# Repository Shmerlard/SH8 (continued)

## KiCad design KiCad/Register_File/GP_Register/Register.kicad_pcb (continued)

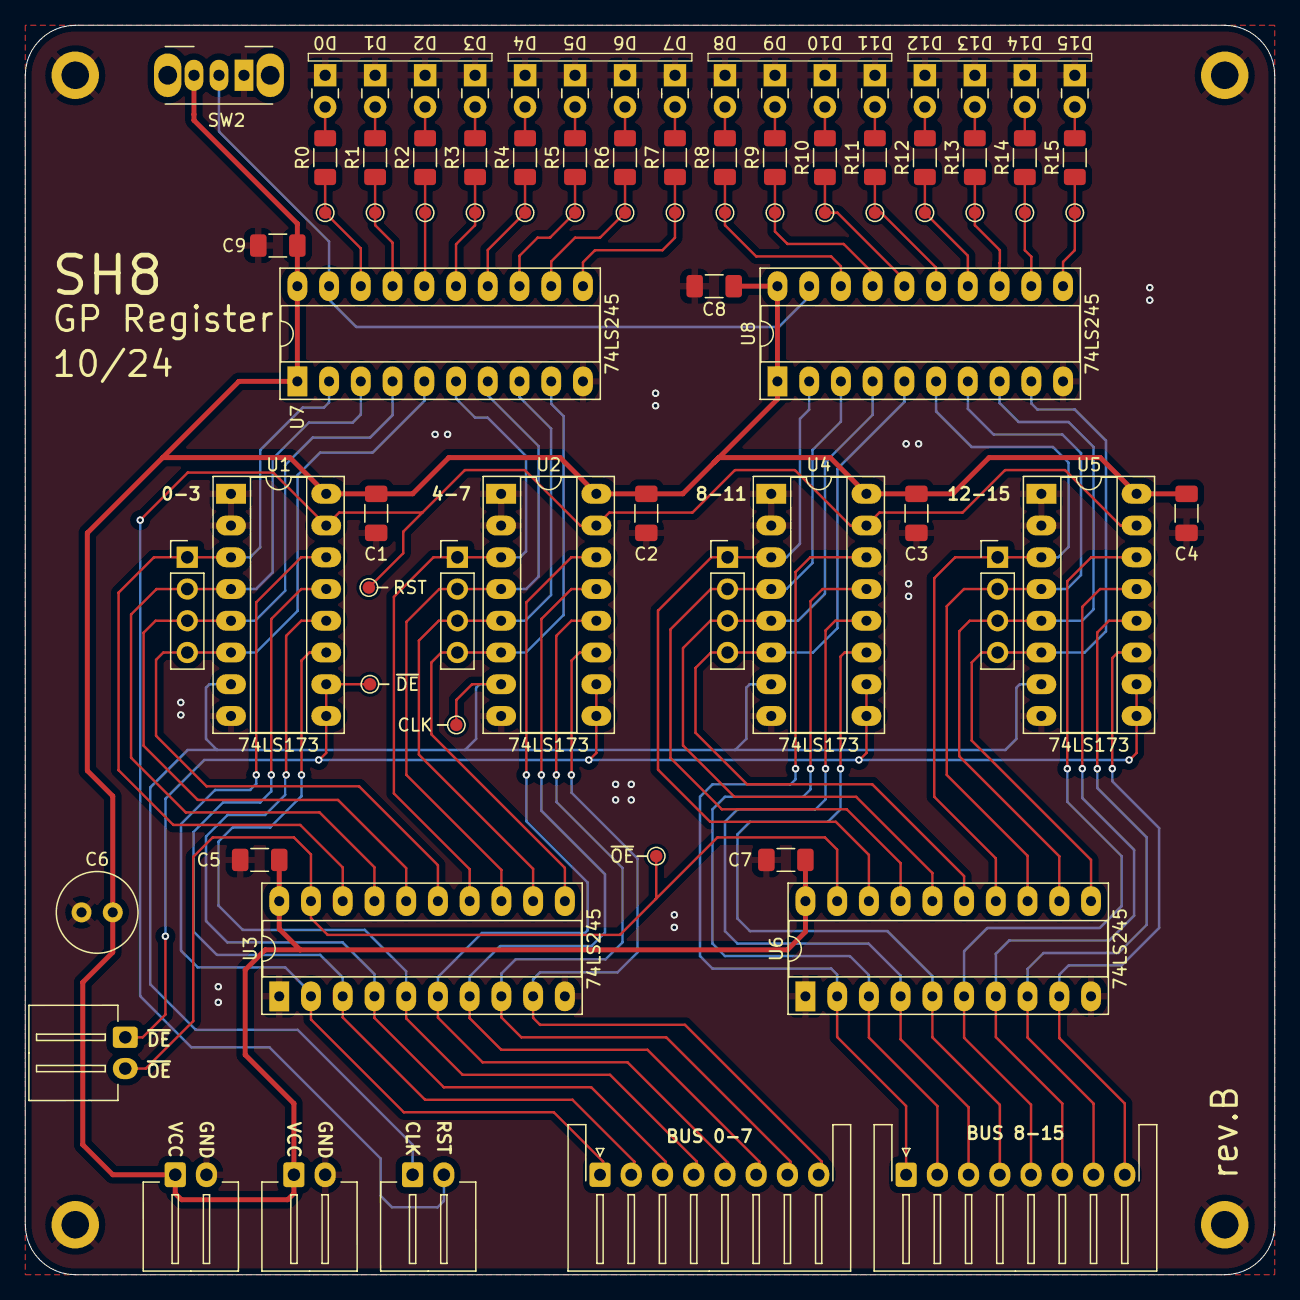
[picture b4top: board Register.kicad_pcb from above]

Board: 2 copper layers, 100.0 x 100.0 mm, 84 parts (0 on the bottom side), 71 nets.

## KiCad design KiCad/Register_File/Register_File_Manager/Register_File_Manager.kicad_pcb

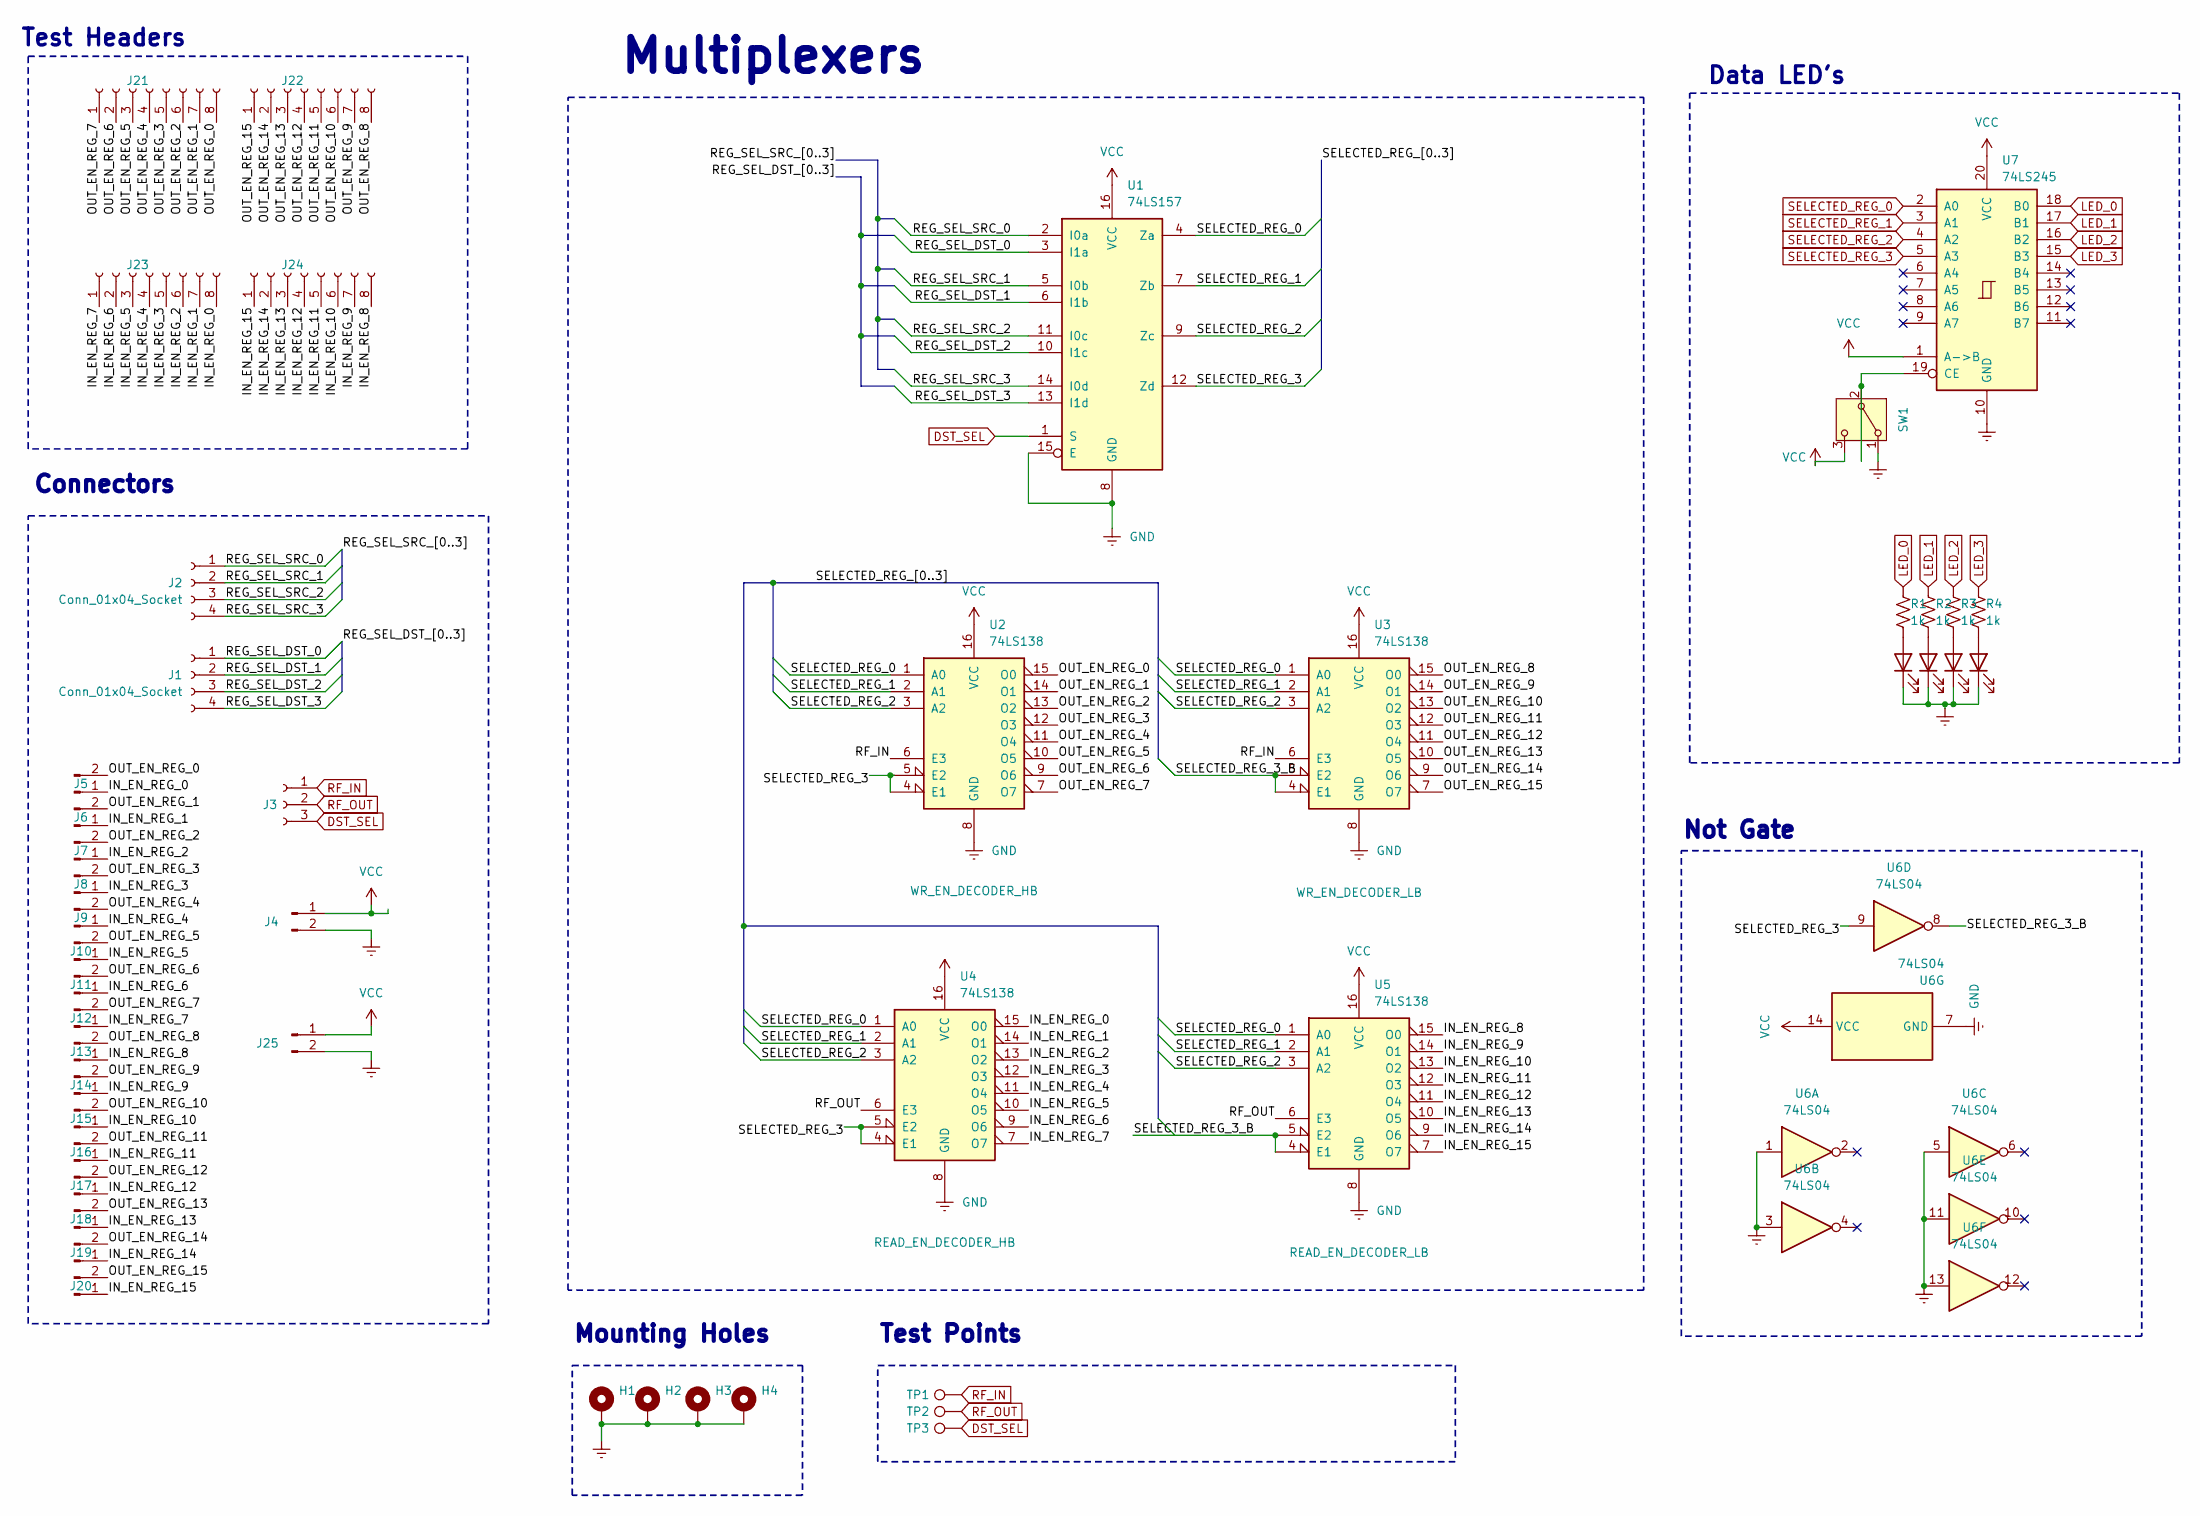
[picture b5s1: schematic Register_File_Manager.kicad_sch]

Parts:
D1, D2, D3, D4: LED; LED_Rectangular_W3.0mm_H2.0mm
H1, H2, H3, H4: MountingHole_Pad; MountingHole_2.2mm_M2_DIN965_Pad
J1, J2: Conn_01x04_Socket; JST_XH_S4B-XH-A-1_1x04_P2.50mm_Horizontal
J3: Conn_01x03_Socket; JST_XH_S3B-XH-A-1_1x03_P2.50mm_Horizontal
J4, J5, J6, J7, J8, J9, J10, J11, J12, J13, J14, J15, J16, J17, J18, J19, J20, J25: Conn_01x02_Socket; JST_XH_S2B-XH-A-1_1x02_P2.50mm_Horizontal
J21, J22, J23, J24: Conn_01x08_Socket; PinHeader_1x08_P2.54mm_Vertical
R1, R2, R3, R4: 1k; R_1206_3216Metric_Pad1.30x1.75mm_HandSolder
SW1: SW_SPDT; SW_Slide_SPDT_Angled_CK_OS102011MA1Q
TP1, TP2, TP3: TestPoint; TestPoint_Pad_D1.0mm
U1: 74LS157; DIP-16_W7.62mm_Socket_LongPads
U2, U3, U4, U5: 74LS138; DIP-16_W7.62mm_Socket_LongPads
U6: 74LS04
U7: 74LS245; DIP-20_W7.62mm_Socket_LongPads

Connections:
/IN_EN_REG_0: J5.1, J23.8, U4.15 (O0)
/IN_EN_REG_1: J6.1, J23.7, U4.14 (O1)
/IN_EN_REG_2: J7.1, J23.6, U4.13 (O2)
/IN_EN_REG_3: J8.1, J23.5, U4.12 (O3)
/IN_EN_REG_4: J9.1, J23.4, U4.11 (O4)
/IN_EN_REG_5: J10.1, J23.3, U4.10 (O5)
/IN_EN_REG_6: J11.1, J23.2, U4.9 (O6)
/IN_EN_REG_7: J12.1, J23.1, U4.7 (O7)
/IN_EN_REG_8: J13.1, J24.8, U5.15 (O0)
/IN_EN_REG_9: J14.1, J24.7, U5.14 (O1)
/IN_EN_REG_10: J15.1, J24.6, U5.13 (O2)
/IN_EN_REG_11: J16.1, J24.5, U5.12 (O3)
/IN_EN_REG_12: J17.1, J24.4, U5.11 (O4)
/IN_EN_REG_13: J18.1, J24.3, U5.10 (O5)
/IN_EN_REG_14: J19.1, J24.2, U5.9 (O6)
/IN_EN_REG_15: J20.1, J24.1, U5.7 (O7)
/OUT_EN_REG_0: J5.2, J21.8, U2.15 (O0)
/OUT_EN_REG_1: J6.2, J21.7, U2.14 (O1)
/OUT_EN_REG_2: J7.2, J21.6, U2.13 (O2)
/OUT_EN_REG_3: J8.2, J21.5, U2.12 (O3)
/OUT_EN_REG_4: J9.2, J21.4, U2.11 (O4)
/OUT_EN_REG_5: J10.2, J21.3, U2.10 (O5)
/OUT_EN_REG_6: J11.2, J21.2, U2.9 (O6)
/OUT_EN_REG_7: J12.2, J21.1, U2.7 (O7)
/OUT_EN_REG_8: J13.2, J22.8, U3.15 (O0)
/OUT_EN_REG_9: J14.2, J22.7, U3.14 (O1)
/OUT_EN_REG_10: J15.2, J22.6, U3.13 (O2)
/OUT_EN_REG_11: J16.2, J22.5, U3.12 (O3)
/OUT_EN_REG_12: J17.2, J22.4, U3.11 (O4)
/OUT_EN_REG_13: J18.2, J22.3, U3.10 (O5)
/OUT_EN_REG_14: J19.2, J22.2, U3.9 (O6)
/OUT_EN_REG_15: J20.2, J22.1, U3.7 (O7)
/REG_SEL_DST_0: J1.1, U1.3 (I1a)
/REG_SEL_DST_1: J1.2, U1.6 (I1b)
/REG_SEL_DST_2: J1.3, U1.10 (I1c)
/REG_SEL_DST_3: J1.4, U1.13 (I1d)
/REG_SEL_SRC_0: J2.1, U1.2 (I0a)
/REG_SEL_SRC_1: J2.2, U1.5 (I0b)
/REG_SEL_SRC_2: J2.3, U1.11 (I0c)
/REG_SEL_SRC_3: J2.4, U1.14 (I0d)
/SELECTED_REG_3_B: U3.4 (E1), U3.5 (E2), U5.4 (E1), U5.5 (E2), U6.8
DST_SEL: J3.3, TP3.1, U1.1 (S)
GND: D1.1 (K), D2.1 (K), D3.1 (K), D4.1 (K), H1.1, H2.1, H3.1, H4.1, J4.2, J25.2, SW1.1 (A), U1.8 (GND), U1.15 (E), U2.8 (GND), U3.8 (GND), U4.8 (GND), U5.8 (GND), U6.1, U6.3, U6.5, U6.7 (GND), U6.11, U6.13, U7.10 (GND)
LED_0: R1.1, U7.18 (B0)
LED_1: R2.1, U7.17 (B1)
LED_2: R3.1, U7.16 (B2)
LED_3: R4.1, U7.15 (B3)
unnamed: D1.2 (A), R1.2
unnamed: D2.2 (A), R2.2
unnamed: D3.2 (A), R3.2
unnamed: D4.2 (A), R4.2
unnamed: SW1.2 (B), U7.19 (CE)
RF_IN: J3.1, TP1.1, U2.6 (E3), U3.6 (E3)
RF_OUT: J3.2, TP2.1, U4.6 (E3), U5.6 (E3)
SELECTED_REG_0: U1.4 (Za), U2.1 (A0), U3.1 (A0), U4.1 (A0), U5.1 (A0), U7.2 (A0)
SELECTED_REG_1: U1.7 (Zb), U2.2 (A1), U3.2 (A1), U4.2 (A1), U5.2 (A1), U7.3 (A1)
SELECTED_REG_2: U1.9 (Zc), U2.3 (A2), U3.3 (A2), U4.3 (A2), U5.3 (A2), U7.4 (A2)
SELECTED_REG_3: U1.12 (Zd), U2.4 (E1), U2.5 (E2), U4.4 (E1), U4.5 (E2), U6.9, U7.5 (A3)
VCC: J4.1, J25.1, SW1.3 (C), U1.16 (VCC), U2.16 (VCC), U3.16 (VCC), U4.16 (VCC), U5.16 (VCC), U6.14 (VCC), U7.1 (A->B), U7.20 (VCC)

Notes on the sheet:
Connectors
Test Points
Mounting Holes
Test Headers
Multiplexers
Data LED's
Not Gate

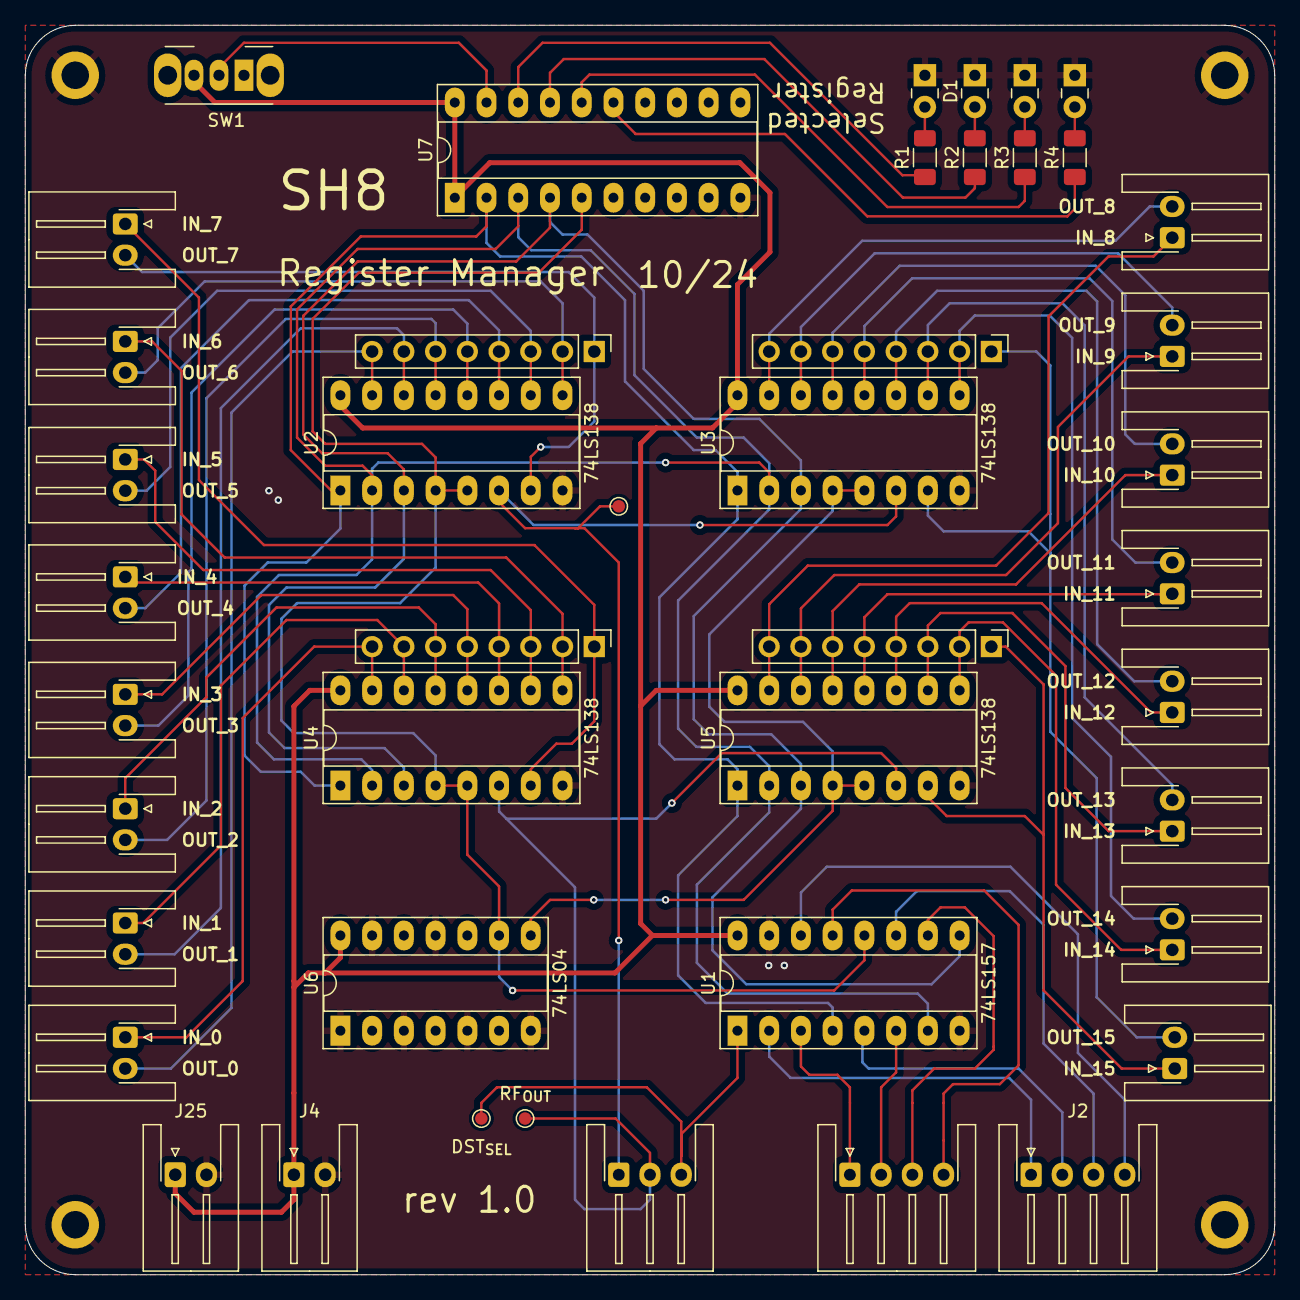
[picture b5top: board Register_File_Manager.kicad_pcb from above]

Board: 2 copper layers, 100.0 x 100.0 mm, 48 parts (0 on the bottom side), 59 nets.

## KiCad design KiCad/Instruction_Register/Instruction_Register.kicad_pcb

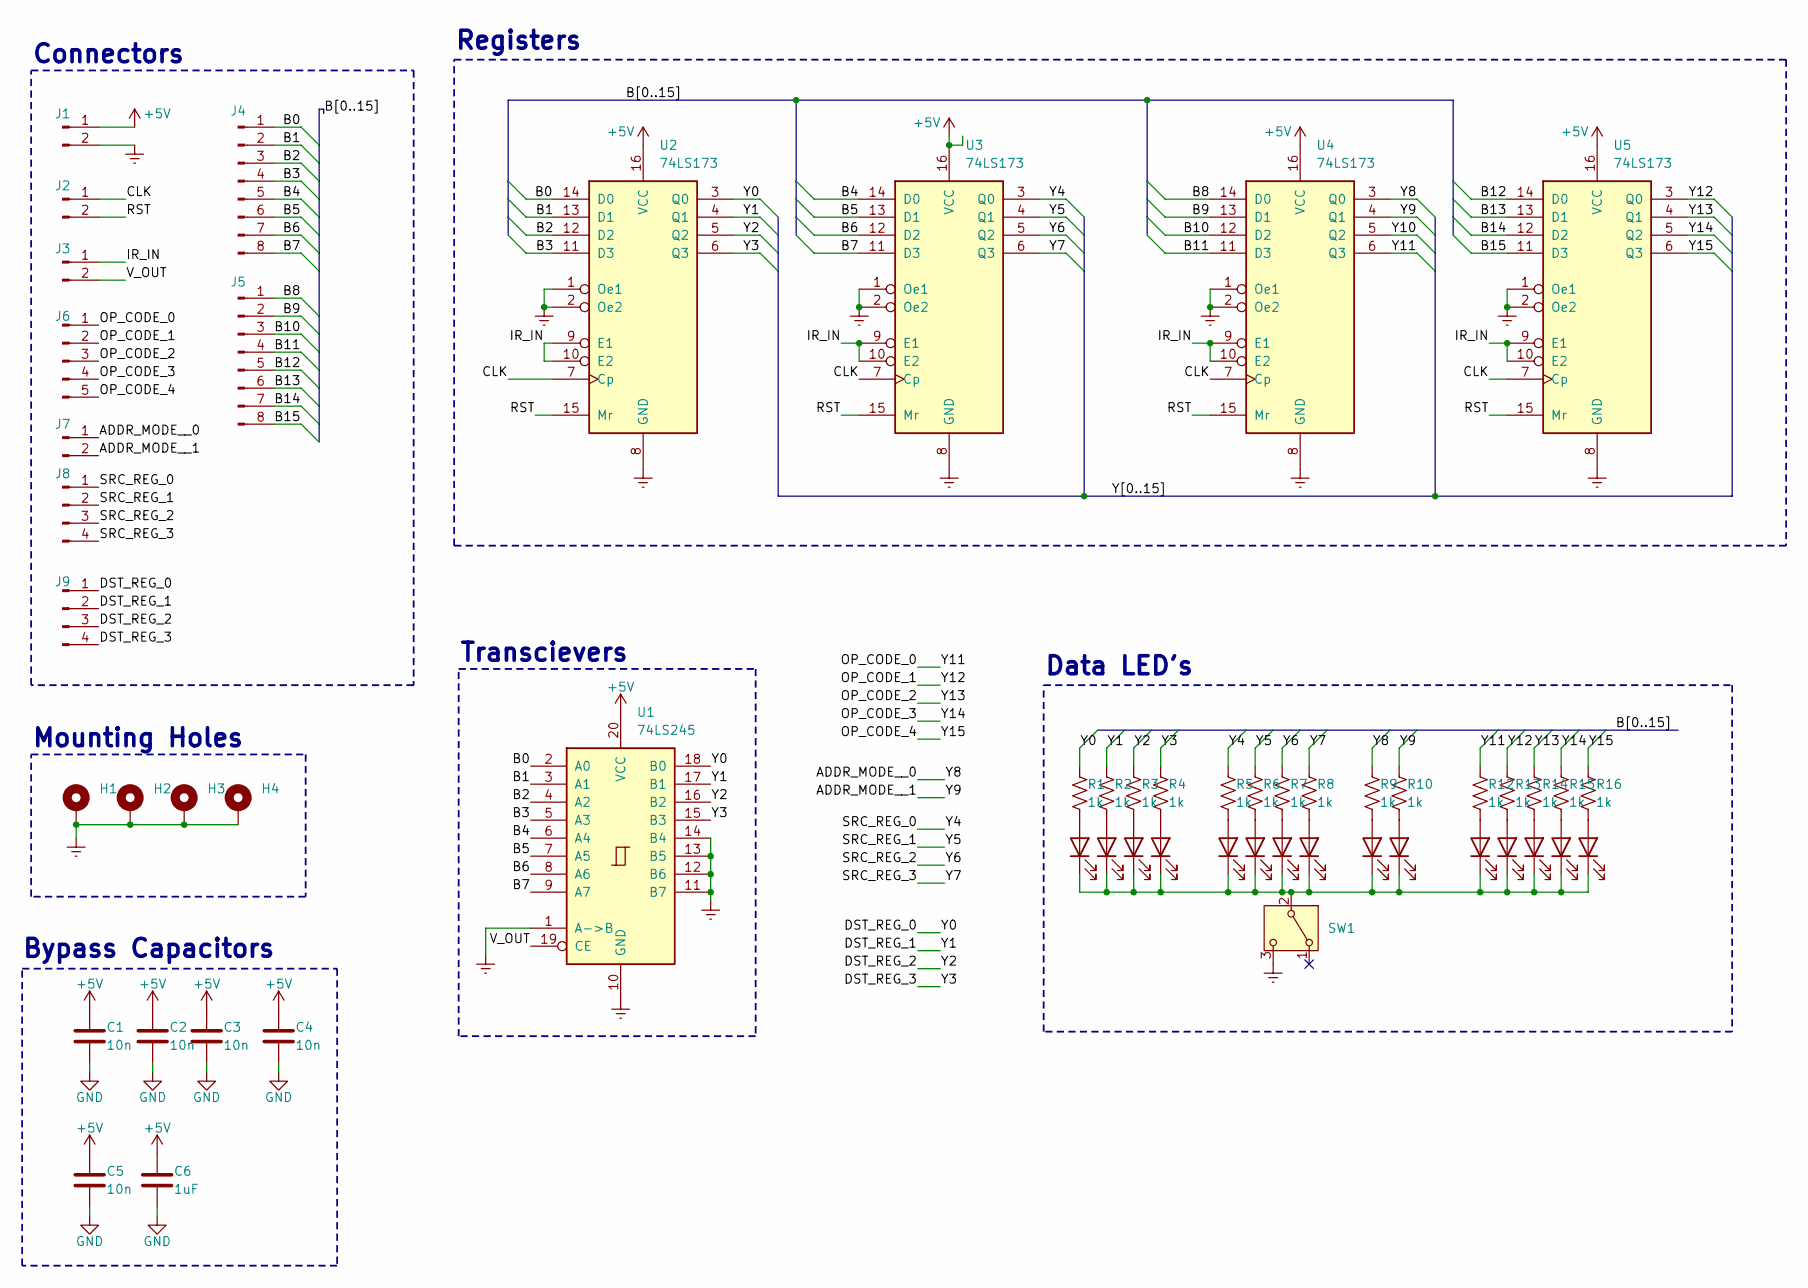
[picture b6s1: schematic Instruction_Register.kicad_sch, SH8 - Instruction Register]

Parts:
C1, C2, C3, C4, C5: 10n; C_Disc_D3.8mm_W2.6mm_P2.50mm
C6: 1uF; C_Radial_D6.3mm_H11.0mm_P2.50mm
D1, D2, D3, D4, D5, D6, D7, D8, D9, D10, D12, D13, D14, D15, D16: LED; LED_Rectangular_W3.0mm_H2.0mm
H1, H2, H3, H4: MountingHole_Pad; MountingHole_2.2mm_M2_DIN965_Pad
J1, J2, J3, J7: Conn_01x02_Pin; JST_XH_S2B-XH-A-1_1x02_P2.50mm_Horizontal
J4, J5: Conn_01x08_Pin; JST_XH_S8B-XH-A-1_1x08_P2.50mm_Horizontal
J6: Conn_01x05_Pin; JST_XH_S5B-XH-A-1_1x05_P2.50mm_Horizontal
J8, J9: Conn_01x04_Pin; JST_XH_S4B-XH-A-1_1x04_P2.50mm_Horizontal
R1, R2, R3, R4, R5, R6, R7, R8, R9, R10, R12, R13, R14, R15, R16: 1k; R_Axial_DIN0204_L3.6mm_D1.6mm_P7.62mm_Horizontal
SW1: SW_SPDT; SW_Slide_SPDT_Angled_CK_OS102011MA1Q
U1: 74LS245; DIP-20_W7.62mm_Socket_LongPads
U2, U3, U4, U5: 74LS173; DIP-16_W7.62mm_Socket_LongPads

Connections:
+5V: C1.1, C2.1, C3.1, C4.1, C5.1, C6.1, J1.1, U1.20 (VCC), U2.16 (VCC), U3.16 (VCC), U4.16 (VCC), U5.16 (VCC)
/B0: J4.1, U1.2 (A0), U2.14 (D0)
/B1: J4.2, U1.3 (A1), U2.13 (D1)
/B2: J4.3, U1.4 (A2), U2.12 (D2)
/B3: J4.4, U1.5 (A3), U2.11 (D3)
/B4: J4.5, U1.6 (A4), U3.14 (D0)
/B5: J4.6, U1.7 (A5), U3.13 (D1)
/B6: J4.7, U1.8 (A6), U3.12 (D2)
/B7: J4.8, U1.9 (A7), U3.11 (D3)
/B8: J5.1, U4.14 (D0)
/B9: J5.2, U4.13 (D1)
/B10: J5.3, U4.12 (D2)
/B11: J5.4, U4.11 (D3)
/B12: J5.5, U5.14 (D0)
/B13: J5.6, U5.13 (D1)
/B14: J5.7, U5.12 (D2)
/B15: J5.8, U5.11 (D3)
/CLK: J2.1, U2.7 (Cp), U3.7 (Cp), U4.7 (Cp), U5.7 (Cp)
/IR_IN: J3.1, U2.9 (E1), U2.10 (E2), U3.9 (E1), U3.10 (E2), U4.9 (E1), U4.10 (E2), U5.9 (E1), U5.10 (E2)
/RST: J2.2, U2.15 (Mr), U3.15 (Mr), U4.15 (Mr), U5.15 (Mr)
/V_OUT: J3.2, U1.19 (CE)
/Y0: J9.1, R1.1, U1.18 (B0), U2.3 (Q0)
/Y1: J9.2, R2.1, U1.17 (B1), U2.4 (Q1)
/Y2: J9.3, R3.1, U1.16 (B2), U2.5 (Q2)
/Y3: J9.4, R4.1, U1.15 (B3), U2.6 (Q3)
/Y4: J8.1, R5.1, U3.3 (Q0)
/Y5: J8.2, R6.1, U3.4 (Q1)
/Y6: J8.3, R7.1, U3.5 (Q2)
/Y7: J8.4, R8.1, U3.6 (Q3)
/Y8: J7.1, R9.1, U4.3 (Q0)
/Y9: J7.2, R10.1, U4.4 (Q1)
/Y10: U4.5 (Q2)
/Y11: J6.1, R12.1, U4.6 (Q3)
/Y12: J6.2, R13.1, U5.3 (Q0)
/Y13: J6.3, R14.1, U5.4 (Q1)
/Y14: J6.4, R15.1, U5.5 (Q2)
/Y15: J6.5, R16.1, U5.6 (Q3)
GND: C1.2, C2.2, C3.2, C4.2, C5.2, C6.2, H1.1, H2.1, H3.1, H4.1, J1.2, SW1.3 (C), U1.1 (A->B), U1.10 (GND), U1.11 (B7), U1.12 (B6), U1.13 (B5), U1.14 (B4), U2.1 (Oe1), U2.2 (Oe2), U2.8 (GND), U3.1 (Oe1), U3.2 (Oe2), U3.8 (GND), U4.1 (Oe1), U4.2 (Oe2), U4.8 (GND), U5.1 (Oe1), U5.2 (Oe2), U5.8 (GND)
unnamed: D1.2 (A), R1.2
unnamed: D1.1 (K), D2.1 (K), D3.1 (K), D4.1 (K), D5.1 (K), D6.1 (K), D7.1 (K), D8.1 (K), D9.1 (K), D10.1 (K), D12.1 (K), D13.1 (K), D14.1 (K), D15.1 (K), D16.1 (K), SW1.2 (B)
unnamed: D2.2 (A), R2.2
unnamed: D3.2 (A), R3.2
unnamed: D4.2 (A), R4.2
unnamed: D5.2 (A), R5.2
unnamed: D6.2 (A), R6.2
unnamed: D7.2 (A), R7.2
unnamed: D8.2 (A), R8.2
unnamed: D9.2 (A), R9.2
unnamed: D10.2 (A), R10.2
unnamed: D12.2 (A), R12.2
unnamed: D13.2 (A), R13.2
unnamed: D14.2 (A), R14.2
unnamed: D15.2 (A), R15.2
unnamed: D16.2 (A), R16.2

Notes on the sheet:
Connectors
Mounting Holes
Data LED's
Bypass Capacitors
Transcievers
Registers

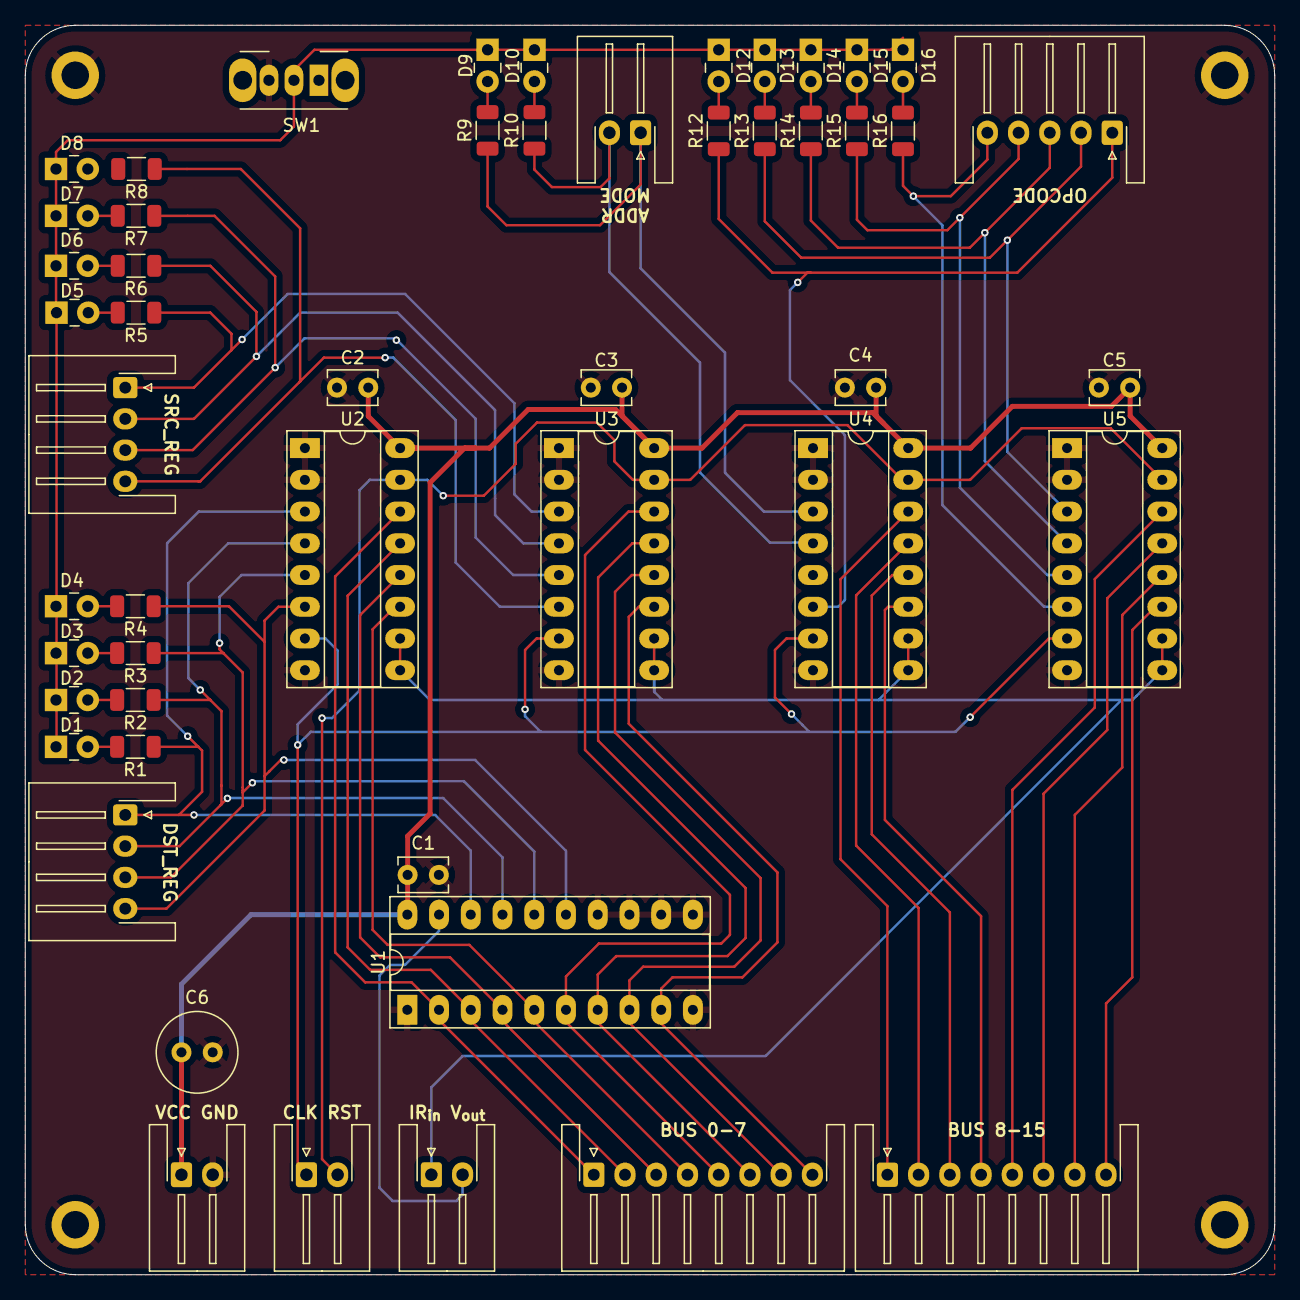
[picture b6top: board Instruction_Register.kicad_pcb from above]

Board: 2 copper layers, 100.0 x 100.0 mm, 55 parts (0 on the bottom side), 53 nets.

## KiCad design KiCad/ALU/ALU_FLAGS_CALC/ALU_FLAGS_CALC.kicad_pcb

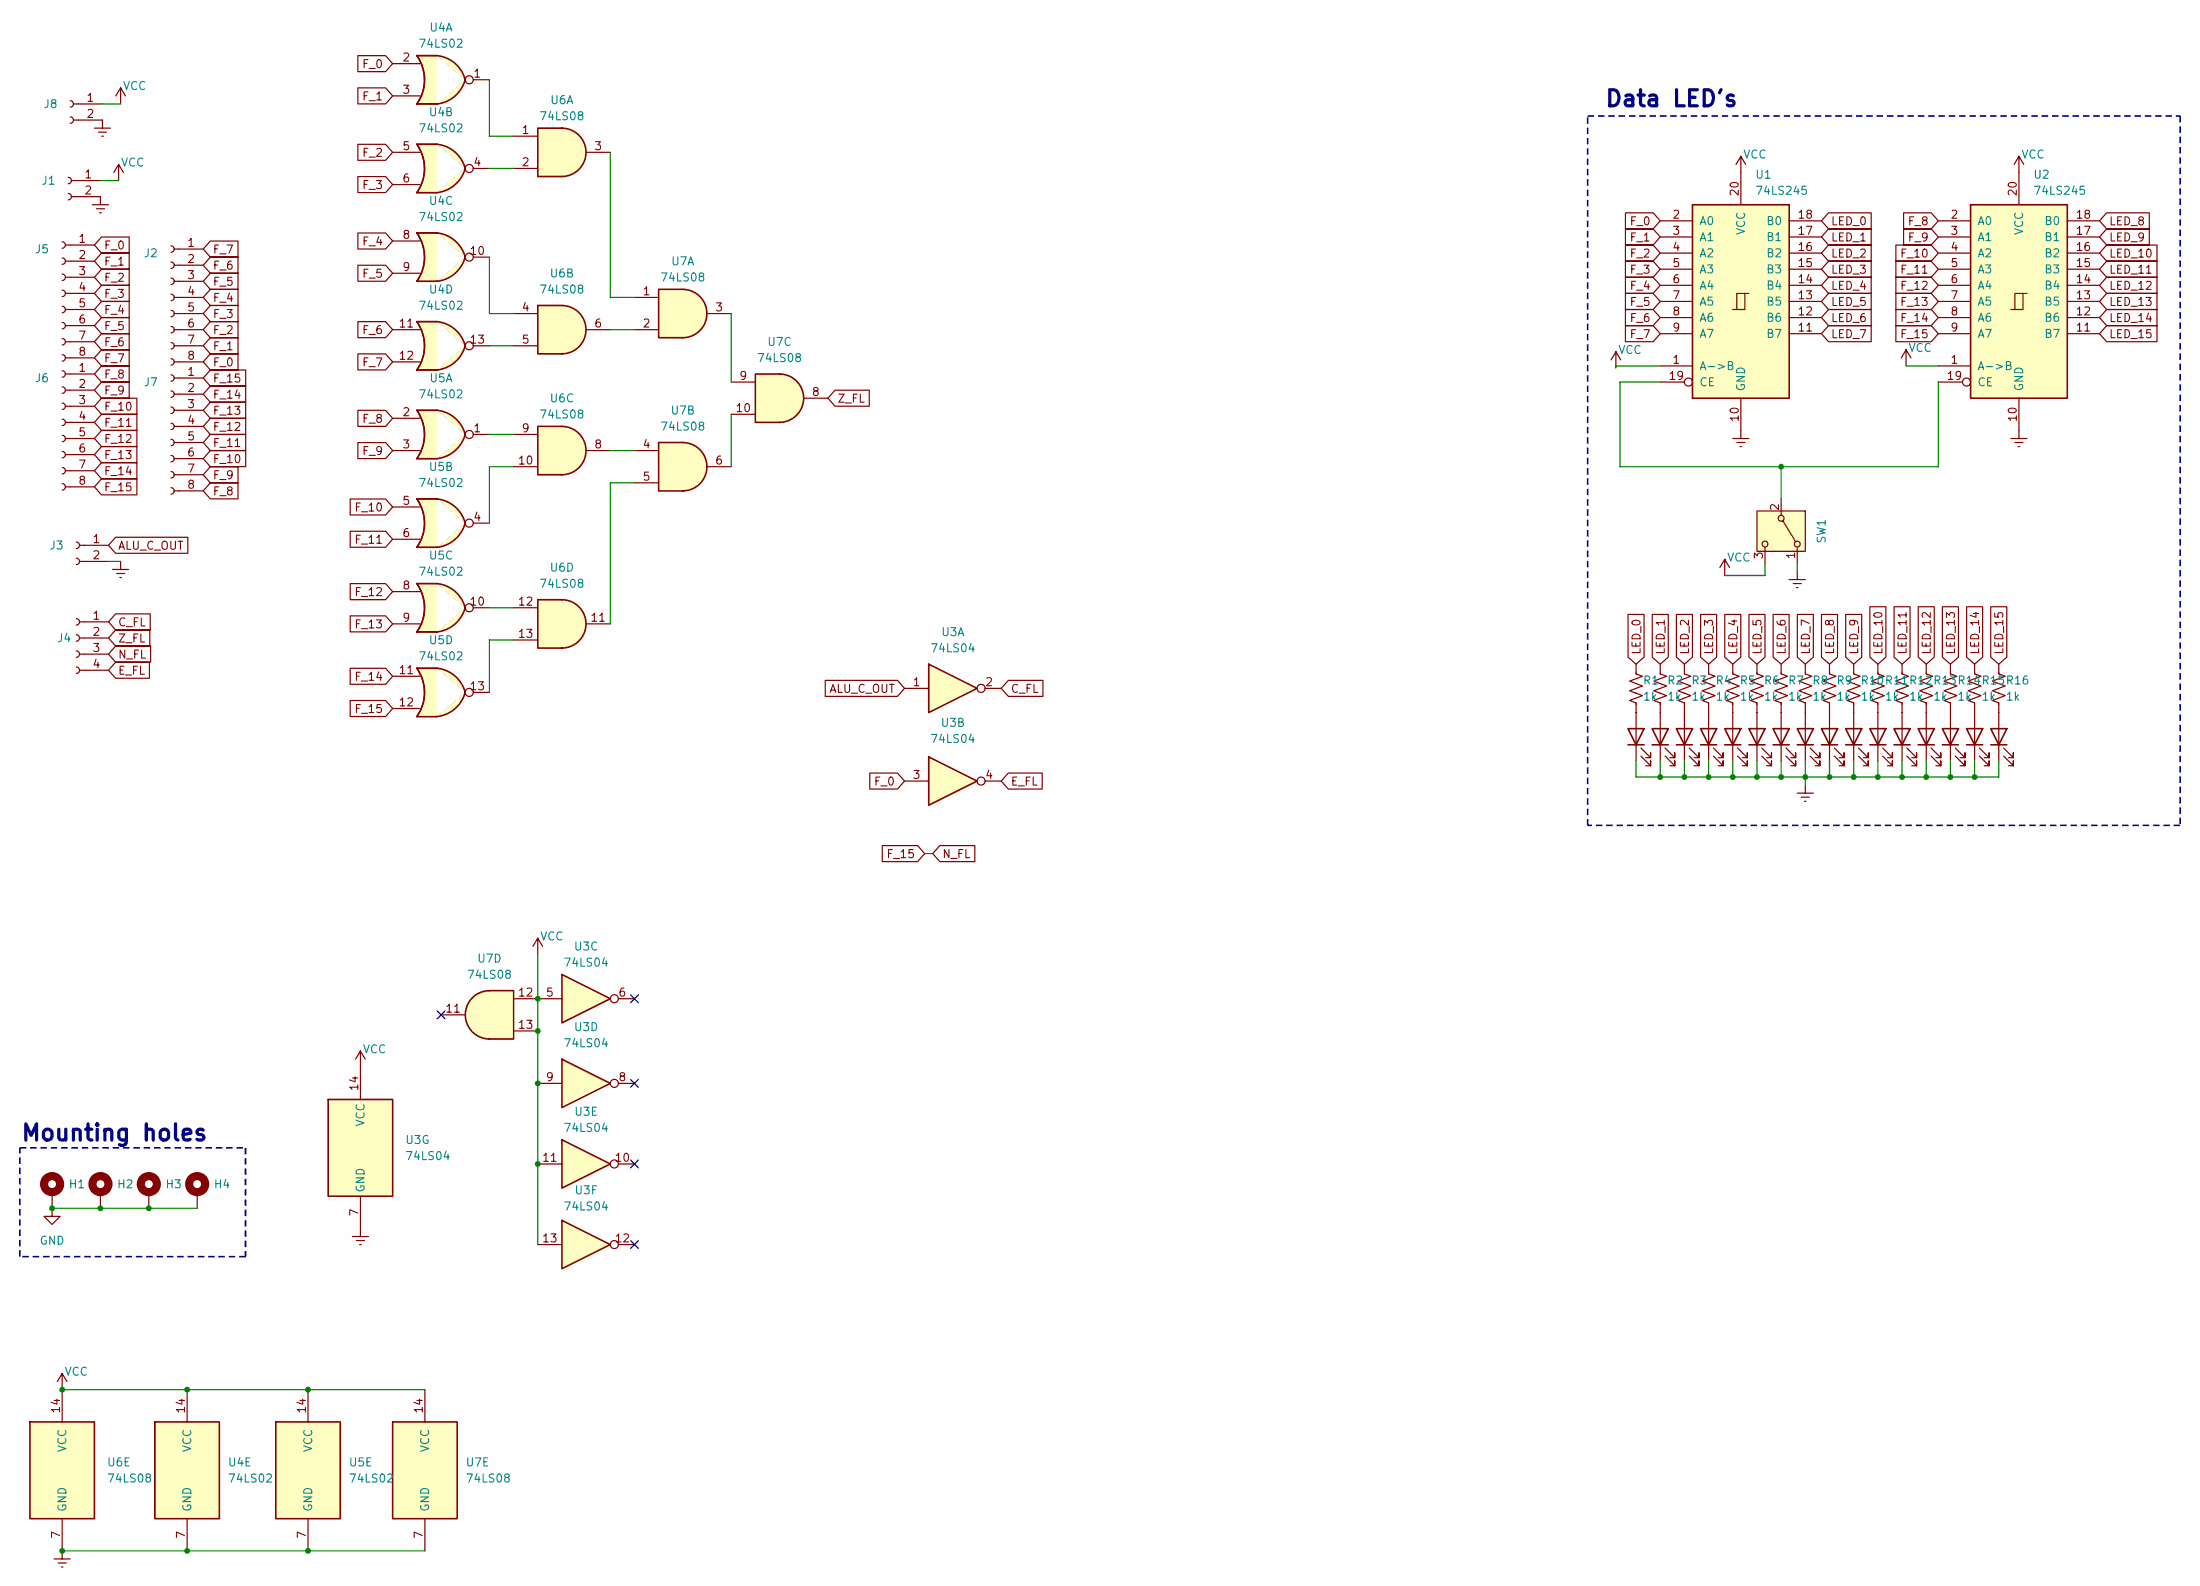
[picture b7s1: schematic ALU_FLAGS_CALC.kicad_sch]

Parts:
D1, D2, D3, D4, D5, D6, D7, D8, D9, D10, D11, D12, D13, D14, D15, D16: LED; LED_Rectangular_W3.0mm_H2.0mm
H1, H2, H3, H4: MountingHole_Pad; MountingHole_2.2mm_M2_DIN965_Pad
J1, J3, J8: Conn_01x02_Socket; JST_XH_S2B-XH-A-1_1x02_P2.50mm_Horizontal
J2, J5, J6, J7: Conn_01x08_Socket; jst_xh_s8b_smd
J4: Conn_01x04_Socket; JST_XH_S4B-XH-A-1_1x04_P2.50mm_Horizontal
R1, R2, R3, R4, R5, R6, R7, R8, R9, R10, R11, R12, R13, R14, R15, R16: 1k; R_1206_3216Metric_Pad1.30x1.75mm_HandSolder
SW1: SW_SPDT; SW_Slide_SPDT_Angled_CK_OS102011MA1Q
U1, U2: 74LS245; DIP-20_W7.62mm_Socket_LongPads
U3: 74LS04; DIP-14_W7.62mm_Socket_LongPads
U4, U5: 74LS02; DIP-14_W7.62mm_Socket_LongPads
U6, U7: 74LS08; DIP-14_W7.62mm_Socket_LongPads

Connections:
ALU_C_OUT: J3.1, U3.1
C_FL: J4.1, U3.2
E_FL: J4.4, U3.4
F_0: J2.8, J5.1, U1.2 (A0), U3.3, U4.2
F_1: J2.7, J5.2, U1.3 (A1), U4.3
F_2: J2.6, J5.3, U1.4 (A2), U4.5
F_3: J2.5, J5.4, U1.5 (A3), U4.6
F_4: J2.4, J5.5, U1.6 (A4), U4.8
F_5: J2.3, J5.6, U1.7 (A5), U4.9
F_6: J2.2, J5.7, U1.8 (A6), U4.11
F_7: J2.1, J5.8, U1.9 (A7), U4.12
F_8: J6.1, J7.8, U2.2 (A0), U5.2
F_9: J6.2, J7.7, U2.3 (A1), U5.3
F_10: J6.3, J7.6, U2.4 (A2), U5.5
F_11: J6.4, J7.5, U2.5 (A3), U5.6
F_12: J6.5, J7.4, U2.6 (A4), U5.8
F_13: J6.6, J7.3, U2.7 (A5), U5.9
F_14: J6.7, J7.2, U2.8 (A6), U5.11
F_15: J4.3, J6.8, J7.1, U2.9 (A7), U5.12
GND: D1.1 (K), D2.1 (K), D3.1 (K), D4.1 (K), D5.1 (K), D6.1 (K), D7.1 (K), D8.1 (K), D9.1 (K), D10.1 (K), D11.1 (K), D12.1 (K), D13.1 (K), D14.1 (K), D15.1 (K), D16.1 (K), H1.1, H2.1, H3.1, H4.1, J1.2, J3.2, J8.2, SW1.1 (A), U1.10 (GND), U2.10 (GND), U3.7 (GND), U4.7 (GND), U5.7 (GND), U6.7 (GND), U7.7 (GND)
LED_0: R1.1, U1.18 (B0)
LED_1: R2.1, U1.17 (B1)
LED_2: R3.1, U1.16 (B2)
LED_3: R4.1, U1.15 (B3)
LED_4: R5.1, U1.14 (B4)
LED_5: R6.1, U1.13 (B5)
LED_6: R7.1, U1.12 (B6)
LED_7: R8.1, U1.11 (B7)
LED_8: R9.1, U2.18 (B0)
LED_9: R10.1, U2.17 (B1)
LED_10: R11.1, U2.16 (B2)
LED_11: R12.1, U2.15 (B3)
LED_12: R13.1, U2.14 (B4)
LED_13: R14.1, U2.13 (B5)
LED_14: R15.1, U2.12 (B6)
LED_15: R16.1, U2.11 (B7)
unnamed: D1.2 (A), R1.2
unnamed: D2.2 (A), R2.2
unnamed: D3.2 (A), R3.2
unnamed: D4.2 (A), R4.2
unnamed: D5.2 (A), R5.2
unnamed: D6.2 (A), R6.2
unnamed: D7.2 (A), R7.2
unnamed: D8.2 (A), R8.2
unnamed: D9.2 (A), R9.2
unnamed: D10.2 (A), R10.2
unnamed: D11.2 (A), R11.2
unnamed: D12.2 (A), R12.2
unnamed: D13.2 (A), R13.2
unnamed: D14.2 (A), R14.2
unnamed: D15.2 (A), R15.2
unnamed: D16.2 (A), R16.2
unnamed: SW1.2 (B), U1.19 (CE), U2.19 (CE)
unnamed: U4.1, U6.1
unnamed: U4.4, U6.2
unnamed: U4.10, U6.4
unnamed: U4.13, U6.5
unnamed: U5.1, U6.9
unnamed: U5.4, U6.10
unnamed: U5.10, U6.12
unnamed: U5.13, U6.13
unnamed: U6.3, U7.1
unnamed: U6.6, U7.2
unnamed: U6.8, U7.4
unnamed: U6.11, U7.5
unnamed: U7.3, U7.9
unnamed: U7.6, U7.10
VCC: J1.1, J8.1, SW1.3 (C), U1.1 (A->B), U1.20 (VCC), U2.1 (A->B), U2.20 (VCC), U3.5, U3.9, U3.11, U3.13, U3.14 (VCC), U4.14 (VCC), U5.14 (VCC), U6.14 (VCC), U7.12, U7.13, U7.14 (VCC)
Z_FL: J4.2, U7.8

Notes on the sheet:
Data LED's
Mounting holes
